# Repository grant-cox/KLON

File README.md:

# KLON
KiCAD files for KLON Centaur (audio circuit) clone

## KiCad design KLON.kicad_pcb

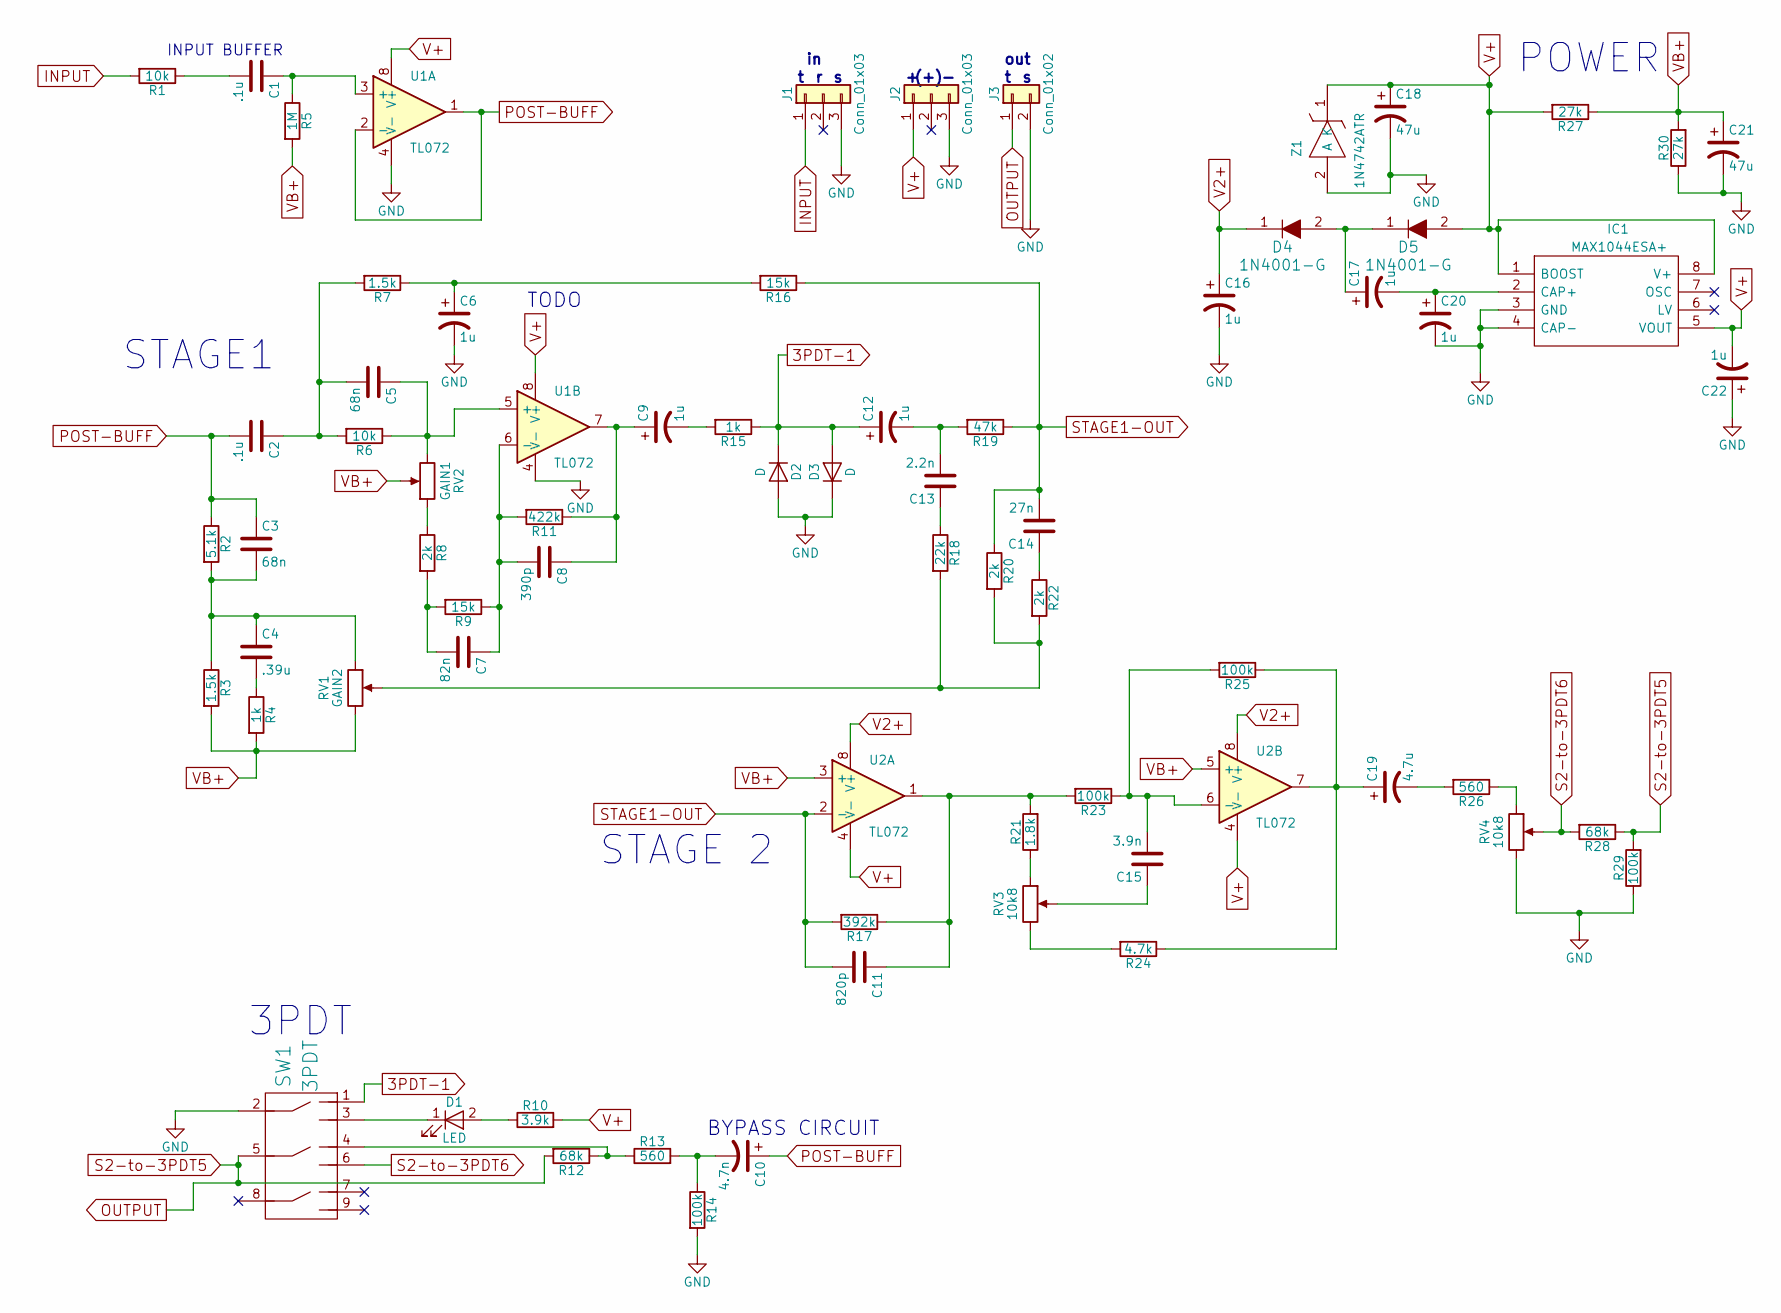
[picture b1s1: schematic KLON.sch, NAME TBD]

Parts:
C1, C2: .1u; C_Rect_L7.0mm_W2.5mm_P5.00mm
C3, C5: 68n; C_Rect_L7.0mm_W2.5mm_P5.00mm
C4: .39u; C_Rect_L7.0mm_W2.5mm_P5.00mm
C6, C9, C12, C16, C17, C20, C22: 1u; CP_Radial_D5.0mm_P2.00mm
C7: 82n; C_Rect_L7.0mm_W2.0mm_P5.00mm
C8: 390p; C_Rect_L7.0mm_W2.5mm_P5.00mm
C10: 4.7n; C_Rect_L7.0mm_W2.0mm_P5.00mm
C11: 820p; C_Rect_L7.0mm_W2.5mm_P5.00mm
C13: 2.2n; C_Rect_L7.0mm_W2.0mm_P5.00mm
C14: 27n; C_Rect_L7.0mm_W2.0mm_P5.00mm
C15: 3.9n; C_Rect_L7.0mm_W2.0mm_P5.00mm
C18, C21: 47u; CP_Radial_D5.0mm_P2.00mm
C19: 4.7u; CP_Radial_D5.0mm_P2.00mm
D1: LED; LED_D1.8mm_W3.3mm_H2.4mm
D2, D3: D; D_A-405_P7.62mm_Horizontal
D4, D5: 1N4001-G; DO-41; MPN 1N4001-G; Digi-Key_PN 641-1310-1-ND
IC1: MAX1044ESA+; DIP-8_W7.62mm_Socket; Manufacturer_Part_Number MAX1044ESA+
J1, J2: Conn_01x03; Socket_Strip_Straight_1x03_Pitch2.54mm
J3: Conn_01x02; Socket_Strip_Straight_1x02_Pitch2.54mm
R1, R6: 10k; R_Axial_DIN0207_L6.3mm_D2.5mm_P10.16mm_Horizontal
R2: 5.1k; R_Axial_DIN0207_L6.3mm_D2.5mm_P10.16mm_Horizontal
R3, R7: 1.5k; R_Axial_DIN0207_L6.3mm_D2.5mm_P10.16mm_Horizontal
R4, R15: 1k; R_Axial_DIN0207_L6.3mm_D2.5mm_P10.16mm_Horizontal
R5: 1M; R_Axial_DIN0207_L6.3mm_D2.5mm_P10.16mm_Horizontal
R8, R20, R22: 2k; R_Axial_DIN0207_L6.3mm_D2.5mm_P10.16mm_Horizontal
R9, R16: 15k; R_Axial_DIN0207_L6.3mm_D2.5mm_P10.16mm_Horizontal
R10: 3.9k; R_Axial_DIN0207_L6.3mm_D2.5mm_P10.16mm_Horizontal
R11: 422k; R_Axial_DIN0207_L6.3mm_D2.5mm_P10.16mm_Horizontal
R12, R28: 68k; R_Axial_DIN0207_L6.3mm_D2.5mm_P10.16mm_Horizontal
R13, R26: 560; R_Axial_DIN0207_L6.3mm_D2.5mm_P10.16mm_Horizontal
R14, R23, R25, R29: 100k; R_Axial_DIN0207_L6.3mm_D2.5mm_P10.16mm_Horizontal
R17: 392k; R_Axial_DIN0207_L6.3mm_D2.5mm_P10.16mm_Horizontal
R18: 22k; R_Axial_DIN0207_L6.3mm_D2.5mm_P10.16mm_Horizontal
R19: 47k; R_Axial_DIN0207_L6.3mm_D2.5mm_P10.16mm_Horizontal
R21: 1.8k; R_Axial_DIN0207_L6.3mm_D2.5mm_P10.16mm_Horizontal
R24: 4.7k; R_Axial_DIN0207_L6.3mm_D2.5mm_P10.16mm_Horizontal
R27, R30: 27k; R_Axial_DIN0207_L6.3mm_D2.5mm_P10.16mm_Horizontal
RV1: GAIN2; Potentiometer_WirePads_Small
RV2: GAIN1; Potentiometer_WirePads_Small
RV3, RV4: 10k8; Potentiometer_WirePads_Small
SW1: 3PDT
U1, U2: TL072; DIP-8_W7.62mm
Z1: 1N4742ATR; DIODEAD1413W86L463D238; Manufacturer_Part_Number 1N4742ATR

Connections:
3PDT-1: C12.1, D2.1 (K), D3.2 (A), R15.1, SW1.1
GND: C6.2, C16.2, C18.2, C20.2, C21.2, C22.1, D2.2 (A), D3.1 (K), IC1.3 (GND), IC1.4 (CAP-), J1.3, J2.3, J3.2, R14.2, R29.1, R30.1, RV4.3, SW1.2, U1.4 (V-), Z1.2 (A)
INPUT: J1.1, R1.2
unnamed: C1.1, R5.1, U1.3 (+)
unnamed: C1.2, R1.1
unnamed: C2.1, C5.2, R6.2, R7.2
unnamed: C3.2, C4.1, R2.2, R3.1, RV1.1
unnamed: C4.2, R4.1
unnamed: C5.1, R6.1, RV2.3, U1.5 (+)
unnamed: C6.1, R7.1, R16.2
unnamed: C7.1, C8.2, R9.1, R11.2, U1.6 (-)
unnamed: C7.2, R8.2, R9.2
unnamed: C8.1, C9.1, R11.1, U1.7
unnamed: C9.2, R15.2
unnamed: C10.2, R13.2, R14.1
unnamed: C11.1, R17.1, R21.2, R23.2, U2.1
unnamed: C12.2, C13.2, R19.2
unnamed: C13.1, R18.1
unnamed: C14.1, R22.1
unnamed: C15.1, RV3.2
unnamed: C15.2, R23.1, R25.2, U2.6 (-)
unnamed: C17.1, D4.2, D5.1
unnamed: C17.2, C20.1, IC1.2 (CAP+)
unnamed: C19.1, R24.1, R25.1, U2.7
unnamed: C19.2, R26.2
unnamed: D1.1 (K), SW1.3
unnamed: D1.2 (A), R10.1
unnamed: R8.1, RV2.1
unnamed: R12.1, R13.1, SW1.4
unnamed: R18.2, R20.2, R22.2, RV1.2
unnamed: R21.1, RV3.1
unnamed: R24.2, RV3.3
unnamed: R26.1, RV4.1
OUTPUT: J3.1, R12.2, R28.1, R29.2, SW1.5
POST-BUFF: C2.2, C3.1, C10.1, R2.1, U1.1, U1.2 (-)
S2-to-3PDT6: R28.2, RV4.2, SW1.6
STAGE1-OUT: C11.2, C14.2, R16.1, R17.2, R19.1, R20.1, U2.2 (-)
V2+: C16.1, D4.1, U2.8 (V+)
V+: C18.1, C22.2, D5.2, IC1.1 (BOOST), IC1.5 (VOUT), IC1.8 (V+), J2.1, R10.2, R27.2, U1.8 (V+), U2.4 (V-), Z1.1 (K)
VB+: C21.1, R3.2, R4.2, R5.2, R27.1, R30.2, RV1.3, RV2.2, U2.3 (+), U2.5 (+)

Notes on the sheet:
INPUT BUFFER
STAGE1
TODO
3PDT
STAGE 2
BYPASS CIRCUIT
POWER
out
(+)

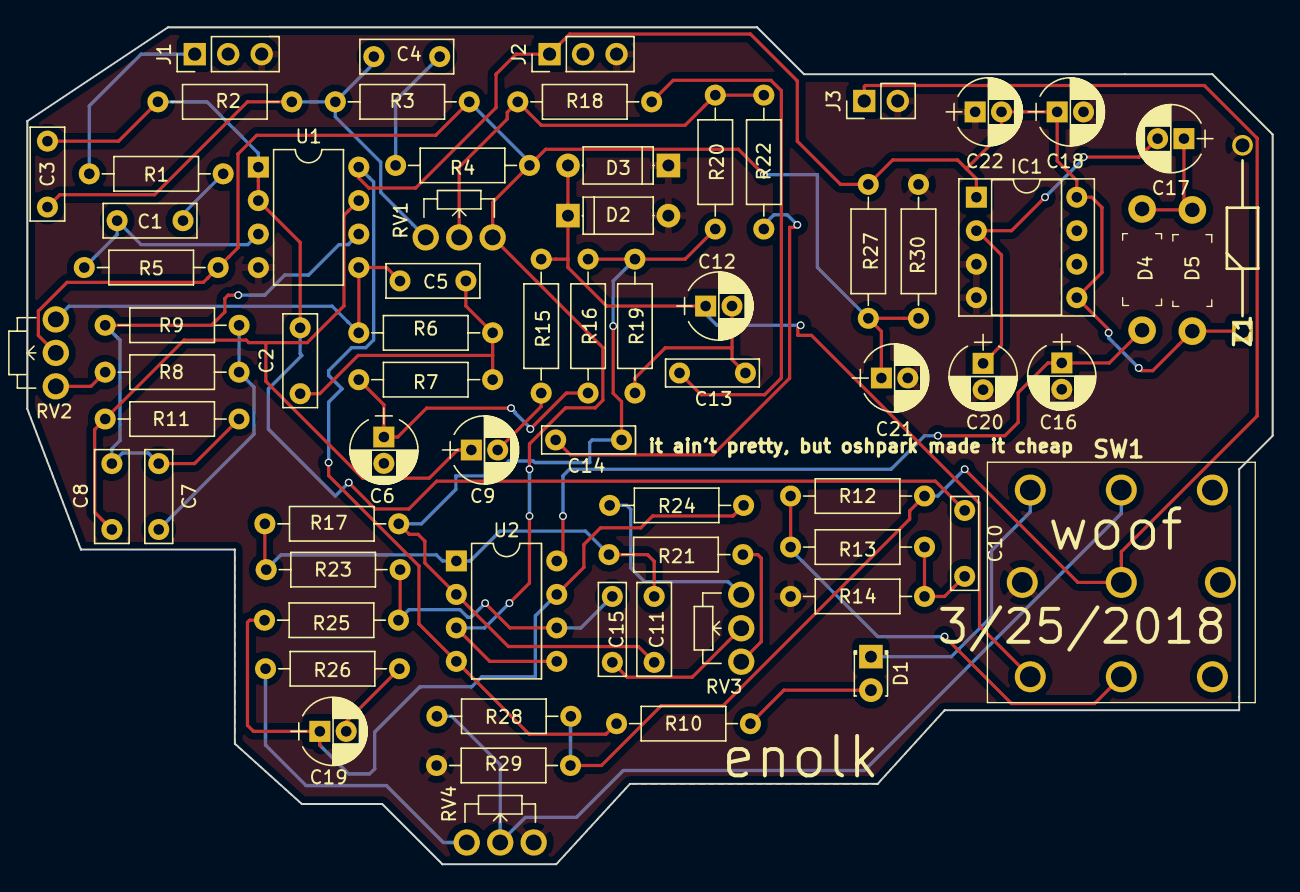
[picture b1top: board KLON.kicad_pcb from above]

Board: 2 copper layers, 94.5 x 63.5 mm, 69 parts (0 on the bottom side), 40 nets.

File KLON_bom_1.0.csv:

Component,Description,Part,References,Value,Footprint,Quantity Per PCB,Datasheet,Category,Status,Family,MPN,Digi-Key_PN,DK_Datasheet_Link,DK_Detail_Page,Manufacturer,Manufacturer_Name,Height,RS Price/Stock,RS Part Number,Manufacturer_Part_Number,Note
1,Unpolarized capacitor,C,C1 C2,.1u,C_Rect_L7.0mm_W2.5mm_P5.00mm,2,,,,,,,,,,,,,,,
2,Unpolarized capacitor,C,C4,.39u,C_Rect_L7.0mm_W2.5mm_P5.00mm,1,,,,,,,,,,,,,,,
3,Polarised capacitor,CP1,C6 C9 C12 C16 C17 C20 C22,1u,CP_Radial_D5.0mm_P2.00mm,7,,,,,,493-10855-1-ND,,,,,,,,,
4,Unpolarized capacitor,C,C13,2.2n,C_Rect_L7.0mm_W2.0mm_P5.00mm,1,,,,,,,,,,,,,,,
5,Unpolarized capacitor,C,C14,27n,C_Rect_L7.0mm_W2.0mm_P5.00mm,1,,,,,,,,,,,,,,,
6,Unpolarized capacitor,C,C15,3.9n,C_Rect_L7.0mm_W2.0mm_P5.00mm,1,,,,,,,,,,,,,,,
7,Unpolarized capacitor,C,C8,390p,C_Rect_L7.0mm_W2.5mm_P5.00mm,1,,,,,,,,,,,,,,,
8,Polarised capacitor,CP1,C10,4.7n,C_Rect_L7.0mm_W2.0mm_P5.00mm,1,,,,,,,,,,,,,,,
9,Polarised capacitor,CP1,C19,4.7u,CP_Radial_D5.0mm_P2.00mm,1,,,,,,,,,,,,,,,
10,Polarised capacitor,CP1,C18 C21,47u,CP_Radial_D5.0mm_P2.00mm,2,,,,,,,,,,,,,,,
11,Unpolarized capacitor,C,C3 C5,68n,C_Rect_L7.0mm_W2.5mm_P5.00mm,2,,,,,,,,,,,,,,,
12,Unpolarized capacitor,C,C11,820p,C_Rect_L7.0mm_W2.5mm_P5.00mm,1,,,,,,,,,,,,,,,
13,Unpolarized capacitor,C,C7,82n,C_Rect_L7.0mm_W2.0mm_P5.00mm,1,,,,,,,,,,,,,,,
14,DIODE GEN PURP 50V 1A DO41,1N4001-G,D4 D5,1N4001-G,DO-41,2,http://www.comchiptech.com/cms/UserFiles/QW-BG013 1N4001 Thru456224. 1N4007 REV.A.pdf,Discrete Semiconductor Products,Active,Diodes - Rectifiers - Single,1N4001-G,641-1310-1-ND,http://www.comchiptech.com/cms/UserFiles/QW-BG013 1N4001 Thru456224. 1N4007 REV.A.pdf,/product-detail/en/comchip-technology/1N4001-G/641-1310-1-ND/1979675,Comchip Technology,,,,,,
15,Diode,D,D2 D3,D,D_A-405_P7.62mm_Horizontal,2,,,,,,,,,,,,,,,
16,LED generic,LED,D1,LED,LED_D1.8mm_W3.3mm_H2.4mm,1,,,,,,,,,,,,,,,
17,Charge Pump Switched Cap 20mA 5V,MAX1044ESA+,IC1,MAX1044ESA+,DIP-8_W7.62mm_Socket,1,http://datasheets.maximintegrated.com/en/ds/ICL7660-MAX1044.pdf,,,,,,,,,Maxim Integrated,1.75,http://uk.rs-online.com/web/p/products/7328481P,7328481P,MAX1044ESA+,
18,"Generic connector, single row, 01x02",Conn_01x02,J3,Conn_01x02,Socket_Strip_Straight_1x02_Pitch2.54mm,1,,,,,,,,,,,,,,,
19,"Generic connector, single row, 01x03",Conn_01x03,J1 J2,Conn_01x03,Socket_Strip_Straight_1x03_Pitch2.54mm,2,,,,,,,,,,,,,,,
20,Resistor,R,R3 R7,1.5k,R_Axial_DIN0207_L6.3mm_D2.5mm_P10.16mm_Horizontal,2,,,,,,,,,,,,,,,
21,Resistor,R,R21,1.8k,R_Axial_DIN0207_L6.3mm_D2.5mm_P10.16mm_Horizontal,1,,,,,,,,,,,,,,,
22,Resistor,R,R14 R23 R25 R29,100k,R_Axial_DIN0207_L6.3mm_D2.5mm_P10.16mm_Horizontal,4,,,,,,,,,,,,,,,
23,Resistor,R,R1 R6,10k,R_Axial_DIN0207_L6.3mm_D2.5mm_P10.16mm_Horizontal,2,,,,,,,,,,,,,,,
24,Resistor,R,R9 R16,15k,R_Axial_DIN0207_L6.3mm_D2.5mm_P10.16mm_Horizontal,2,,,,,,,,,,,,,,,
25,Resistor,R,R5,1M,R_Axial_DIN0207_L6.3mm_D2.5mm_P10.16mm_Horizontal,1,,,,,,,,,,,,,,,
26,Resistor,R,R4 R15,1k,R_Axial_DIN0207_L6.3mm_D2.5mm_P10.16mm_Horizontal,2,,,,,,,,,,,,,,,
27,Resistor,R,R18,22k,R_Axial_DIN0207_L6.3mm_D2.5mm_P10.16mm_Horizontal,1,,,,,,,,,,,,,,,
28,Resistor,R,R27 R30,27k,R_Axial_DIN0207_L6.3mm_D2.5mm_P10.16mm_Horizontal,2,,,,,,,,,,,,,,,
29,Resistor,R,R8 R20 R22,2k,R_Axial_DIN0207_L6.3mm_D2.5mm_P10.16mm_Horizontal,3,,,,,,,,,,,,,,,
30,Resistor,R,R10,3.9k,R_Axial_DIN0207_L6.3mm_D2.5mm_P10.16mm_Horizontal,1,,,,,,,,,,,,,,,
31,Resistor,R,R17,392k,R_Axial_DIN0207_L6.3mm_D2.5mm_P10.16mm_Horizontal,1,,,,,,,,,,,,,,,
32,Resistor,R,R24,4.7k,R_Axial_DIN0207_L6.3mm_D2.5mm_P10.16mm_Horizontal,1,,,,,,,,,,,,,,,
33,Resistor,R,R11,422k,R_Axial_DIN0207_L6.3mm_D2.5mm_P10.16mm_Horizontal,1,,,,,,,,,,,,,,,
34,Resistor,R,R19,47k,R_Axial_DIN0207_L6.3mm_D2.5mm_P10.16mm_Horizontal,1,,,,,,,,,,,,,,,
35,Resistor,R,R2,5.1k,R_Axial_DIN0207_L6.3mm_D2.5mm_P10.16mm_Horizontal,1,,,,,,,,,,,,,,,
36,Resistor,R,R13 R26,560,R_Axial_DIN0207_L6.3mm_D2.5mm_P10.16mm_Horizontal,2,,,,,,,,,,,,,,,
37,Resistor,R,R12 R28,68k,R_Axial_DIN0207_L6.3mm_D2.5mm_P10.16mm_Horizontal,2,,,,,,,,,,,,,,,
38,Potentiometer,POT,RV3 RV4,10k8,Potentiometer_WirePads_Small,2,,,,,,,,,,,,,,,Treble
39,Potentiometer,POT,RV2,GAIN1,Potentiometer_WirePads_Small,1,,,,,,,,,,,,,,,DUAL POT
40,Potentiometer,POT,RV1,GAIN2,Potentiometer_WirePads_Small,1,,,,,,,,,,,,,,,DUAL POT
41,,3PDT,SW1,3PDT,3PDT,1,,,,,,,,,,,,,,,
42,"Dual Operational Amplifiers, DIP-8/SOIC-8/TSSOP-8/VSSOP-8",TL072,U1 U2,TL072,DIP-8_W7.62mm,2,http://www.ti.com/lit/ds/symlink/lm358.pdf,,,,,296-1775-5-ND,,,,,,,,,
43,"Diode, Fairchild, 1N4742ATR Fairchild 1N4742ATR Zener Diode, 12V 5% 1 W Through Hole 2-Pin DO-41",1N4742ATR,Z1,1N4742ATR,DIODEAD1413W86L463D238,1,http://uk.rs-online.com/web/p/products/8050075,,,,,1N4001-TPMSCT-ND,,,,Fairchild Semiconductor,,http://uk.rs-online.com/web/p/products/8050075,8050075,1N4742ATR,
,,,,,,,,,,,,,,,,,,,,,
,,,,,,,,,,,,,,,,,,,,,
Component Groups:,43,,,,,,,,,,,,,,,,,,,,
Component Count:,69,,,,,,,,,,,,,,,,,,,,
Fitted Components:,69,,,,,,,,,,,,,,,,,,,,
Number of PCBs:,1,,,,,,,,,,,,,,,,,,,,
Total components:,69,,,,,,,,,,,,,,,,,,,,
Schematic Version:,1,,,,,,,,,,,,,,,,,,,,
Schematic Date:,,,,,,,,,,,,,,,,,,,,,
BoM Date:,"Monday, March 26, 2018 'PMt' 10:55:55 PM",,,,,,,,,,,,,,,,,,,,
Schematic Source:,/Users/gc/GitHub/KLON/KLON.sch,,,,,,,,,,,,,,,,,,,,
KiCad Version:,Eeschema 4.0.7,,,,,,,,,,,,,,,,,,,,

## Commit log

2018-03-23 Initial Commit
    Initial COmmit
2018-03-23 Adding library for custom 3PDT symbol, must be imported to KiCAD to be seen.
2018-03-23 organization. Fixed Values. Stage 1 is complete.
2018-03-23 Fixed two connections.
2018-03-24 Finished schematic. Needs to be double checked. Added a couple of libs and footprints.
2018-03-25 Changed connectors for in, out, power. Added footprints for several parts. Correlated footprints to parts. Started PCB.
2018-03-25 updates. Going to temporarily remove ground connections in PCB file to make it easier to route.
2018-03-26 Finished .kicad_pcb. Oshpark quote is $45 for 3 boards. Those cuts aren't pretty, but they are cheap.
2018-05-06 added Capacitor Footprints to CSV, added capacitors to digikey BOM (will put link or .xlsx file here later)
2020-06-23 add .gitignore file
